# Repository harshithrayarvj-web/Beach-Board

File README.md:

# Beach-Board 
***Journals are separate files in the repo!***

*They contain most of the extra details*

A very dynamic and adaptable keyboard meant to pack as many punches as it can within it's relatively small form factor. Contains a raspberry pi pico, 68 hot-swapable switches, en ec11 rotary encoder, an sd card socket, and a TFT LCD, while being meant to operate on QMK.

# The idea behind it
As much as modern keyboards have numerous shortcuts and even gestures for other inputs, I felt that a centralized unit that could do almost all of those things, and more, could be very useful to quickly do things in a straight forward way, similar to a streamdeck. I plan on leveraging the keyboard layout to make it more moldable and flexible for complex tasks, even if they have many smaller details. Along with this I wanted to expand on how screens could be used on keyboards, instead of basic simple screens that show just one type of data, such as WPM, without much flavor, I wanted to have a screen that could potentially both add to the aesthetics of the keyboard, and provide a functional use depending on the task at hand. The theme of a beach themed "surf board" was because of my first long term profile picture that I drew, it helped me create an identity online, so I wanted to hint at that with my first proper project being a keyboard.

# Characteristics of keyboard
- 68 switches (epomaker creamy jade)
- TFT LCD - animations and information
- 16mb USB C Pi Pico
- Hotswap sockets
- Ortholinear
- Microsd card socket - expanding storage
- ec11 Rotary Encoder
- QMK (keyboard intended to be easily customizable and versatile)

# Schematic

# PCB (silkscreen)

# Firmware (MAINLY WIP)

Need to remake the layout due to losing the tab and being unable to use the other file, or I need to test it on the website again.
Keyboard layout needed to make Firmware development easier with the QMK configurator.

# Notes
The keyboard's case was designed with a good amount of clearance to make up for any tolerance issues, but that might lead to fitment issues, so try to use glue or filler items to help the keyboard come together cleaner. Although the large parts are made with clearance in mind, smaller parts like the screen support might have tight clearances, so don't be afraid to sand it down or cut off some extra bits of plastic if they don't fit.
Pay attention to how and where the small components solder to (resistors, capacitors, or the mcp), and make sure the solder doesn't short.
Try to keep an eye on how high the pico sits on the board to not make it hit the case or put too much stress on the pins if the pins are slightly off from spec, pushing them down too far might put stress on the attachment points for the pins on the pico.

# Reflection
Although the project is overall much simpler than what I aim to do for the future, it definitely helped me kick start PCB designing and showed me how to make a finished product (for the most part). It isn't perfect, and I knew that, especially since how rigid hardware can be could affect it's versatility and how future proof it is, meanwhile software can be improved constantly, and that's why I aimed for a mostly software centric keyboard, and looking back I think my fears are pretty exaggerated and unfounded in some areas, but my general prediction was true, and my lack of skill with designing parts for the case, mounting holes, or clearances showed a lot, however it is something I wish to improve on for future projects, and my keyboard showed me some issues I can look at for now. 

I think the main difficulty with the project that's worse than designing the hardware was rather finding the parts that were cheap but reliable to get, as some parts seemed cheap but did not have a reliable stock, or had enormous shipping fees (though I did have to compromise on a few things for that due to no other alternatives, and a large portion of cost came from shipping itself unfortunately from things like JLPCB and Aliexpress). This project has showed me where to start now with planning for parts and the overall components I could realistically use, something that's harder to be flexible with than even designing parts for a project, like designing the case around a certain screw/hot insert dimension.

There were also easy things that I really enjoyed to do, like placing down the footprints for the pcb, routing, adding silkscreen art, and designing some simple sections of the hardware (especially decoration, like the waves on the screen case), they were mostly enjoyable outside of trying to find settings or tools for a specific action, but I learned to use onshape and kicad decently now. 

Overall, this project really helped me jump into designing something functional and useful, letting me learn to use software like onshape and kicad, and create a BOM and work out issues with how realistic it would be, the experience is really valuable for future projects I plan on doing. The risks I took for this project like using a TFT LCD and a Microsd socket were confusing and scary due to the probability of missing something essential or something that would protect them, but the risk seems worth it as now I know about pull up resistors, decoupling capacitors, ground pour, and how to better go about routing and placing components to make them as clean as possible (but I won't lie, I like how my PCB looks rendered in white with the routes from the MCP, minus the large amount of small route sections visible, but I'm sure cleaner routing is better looking). Using my experience so far, I wish to make more projects and have them come into the real world, hopefully pushing them to be more and more reliable, efficient, and compact.

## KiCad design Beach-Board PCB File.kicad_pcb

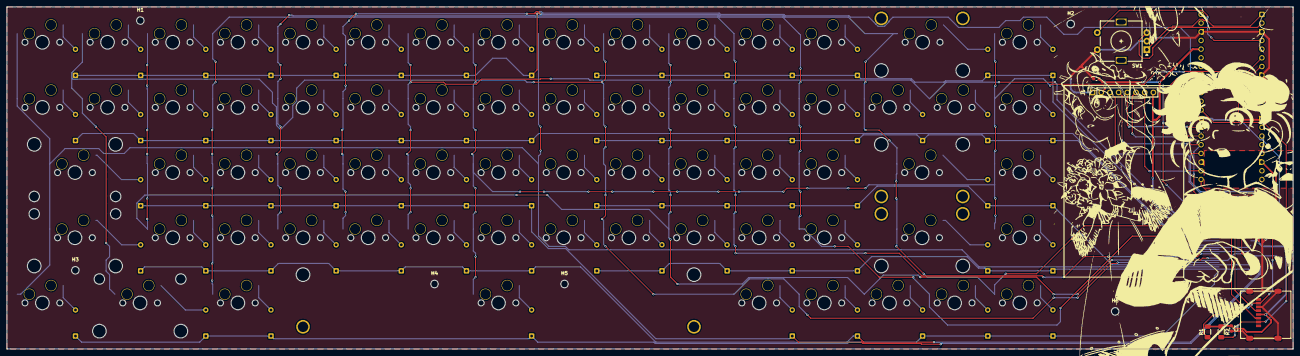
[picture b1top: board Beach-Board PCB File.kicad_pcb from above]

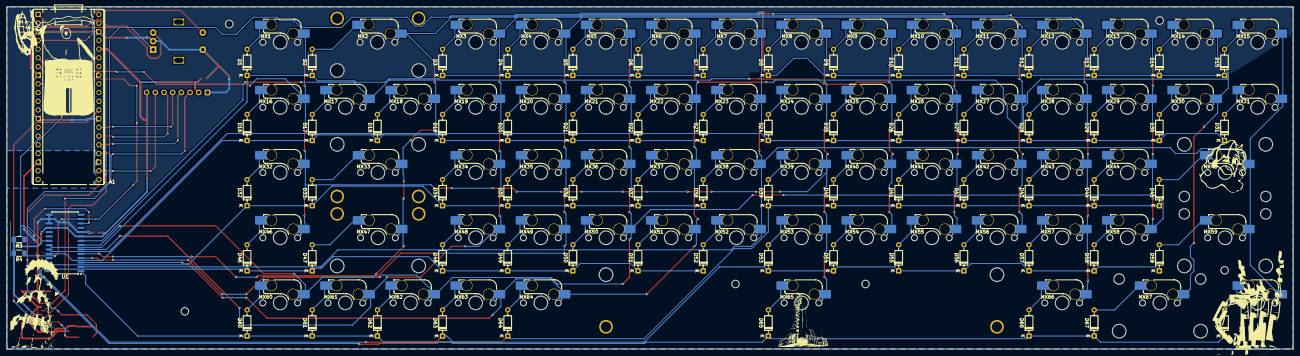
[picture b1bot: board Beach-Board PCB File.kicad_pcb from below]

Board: 2 copper layers, 376.0 x 100.0 mm, 161 parts (147 on the bottom side), 99 nets.

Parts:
A1: RaspberryPi_Pico; RaspberryPi_Pico_Common_THT
C1, C2, C3: 0.1uf; C_0603_1608Metric
D1, D2, D3, D4, D5, D6, D7, D8, D9, D10, D11, D12, D13, D14, D15, D16, D17, D18, D19, D20, D21, D22, D23, D24, D25, D26, D27, D28, D29, D30, D31, D32, D33, D34, D35, D36, D37, D38, D39, D40, D41, D42, D43, D44, D45, D46, D47, D48, D49, D50, D51, D52, D53, D54, D55, D56, D57, D58, D59, D60, D61, D62, D63, D64, D65, D66, D67, D68: 1N4148; D_DO-35_SOD27_P7.62mm_Horizontal
H1, H2, H3, H4, H5, H6: MountingHole; MountingHole_2.2mm_M2
J1: Conn_01x08_Pin; PinSocket_1x08_P2.54mm_Vertical
J2: Micro_SD_Card; microSD_HC_Molex_47219-2001
MX1, MX2, MX3, MX4, MX5, MX6, MX7, MX8, MX9, MX10, MX11, MX12, MX13, MX14, MX15, MX16, MX17, MX18, MX19, MX20, MX21, MX22, MX23, MX24, MX25, MX26, MX27, MX28, MX29, MX30, MX31, MX32, MX33, MX34, MX35, MX36, MX37, MX38, MX39, MX40, MX41, MX42, MX43, MX44, MX45, MX46, MX47, MX48, MX49, MX50, MX51, MX52, MX53, MX54, MX55, MX56, MX57, MX58, MX59, MX60, MX61, MX62, MX63, MX64, MX65, MX66, MX67, MX68: MX_SW_HS; SW_MX_HS_CPG151101S11_1u
R1, R2: 10K; R_1206_3216Metric_Pad1.30x1.75mm_HandSolder
R3, R4: 4.7K; R_1206_3216Metric_Pad1.30x1.75mm_HandSolder
S1, S2, S4: MX_stab; STAB_MX_P_2u
S3, S5, S7: MX_stab; STAB_MX_2u
S6: MX_stab; STAB_MX_P_7u
SW1: RotaryEncoder_Switch; RotaryEncoder_Alps_EC11E-Switch_Vertical_H20mm
U1: MCP23017x-x-SO; SOIC-28W_7.5x17.9mm_P1.27mm

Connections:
/3V3: A1.36 (3V3), C1.1, C2.1, C3.1, J1.2, J1.8, J2.4 (VDD), R1.2, R2.1, R3.2, R4.2, U1.9 (V_{DD}), U1.18 (~RESET)
/CD/DAT3: A1.29 (GPIO22), J2.2 (DAT3/CD), R2.2
/CLK: A1.24 (GPIO18), J1.3, J2.5 (CLK)
/CMD: A1.25 (GPIO19), J1.4, J2.3 (CMD)
/CS: A1.22 (GPIO17), J1.7
/Column_0: MX7.1, MX15.1, MX23.1, MX31.1, MX38.1, MX45.1, MX52.1, MX59.1, MX68.1, U1.2 (GPB1)
/Column_1: MX6.1, MX14.1, MX22.1, MX30.1, MX37.1, MX51.1, MX63.1, MX64.1, MX67.1, U1.3 (GPB2)
/Column_2: MX5.1, MX13.1, MX21.1, MX29.1, MX36.1, MX44.1, MX50.1, MX58.1, MX62.1, U1.4 (GPB3)
/Column_3: MX4.1, MX12.1, MX20.1, MX28.1, MX35.1, MX43.1, MX49.1, MX57.1, MX66.1, U1.5 (GPB4)
/Column_4: MX3.1, MX11.1, MX19.1, MX27.1, MX34.1, MX42.1, MX48.1, MX56.1, MX61.1, U1.6 (GPB5)
/Column_5: MX2.1, MX10.1, MX18.1, MX26.1, MX33.1, MX41.1, MX47.1, MX55.1, MX60.1, U1.7 (GPB6)
/Column_6: MX9.1, MX17.1, MX25.1, MX40.1, MX54.1, U1.8 (GPB7)
/Column_7: A1.9 (GPIO6), MX1.1, MX8.1, MX16.1, MX24.1, MX32.1, MX39.1, MX46.1, MX53.1, MX65.1
/DAT0: A1.21 (GPIO16), J2.7 (DAT0), R1.1
/D/C: A1.26 (GPIO20), J1.6
/RST: A1.27 (GPIO21), J1.5
/Rot-pin_A: A1.1 (GPIO0), SW1.A
/Rot-pin_B: A1.2 (GPIO1), SW1.B
/Rot-pin_S1: A1.4 (GPIO2), SW1.S1
/Row_0: D8.1 (K), D9.1 (K), D10.1 (K), D11.1 (K), D12.1 (K), D13.1 (K), D14.1 (K), D15.1 (K), U1.21 (GPA0)
/Row_1: D1.1 (K), D2.1 (K), D3.1 (K), D4.1 (K), D5.1 (K), D6.1 (K), D7.1 (K), U1.22 (GPA1)
/Row_2: D24.1 (K), D25.1 (K), D26.1 (K), D27.1 (K), D28.1 (K), D29.1 (K), D30.1 (K), D31.1 (K), U1.23 (GPA2)
/Row_3: D16.1 (K), D17.1 (K), D18.1 (K), D19.1 (K), D20.1 (K), D21.1 (K), D22.1 (K), D23.1 (K), U1.24 (GPA3)
/Row_4: D39.1 (K), D40.1 (K), D41.1 (K), D42.1 (K), D43.1 (K), D44.1 (K), D45.1 (K), D64.1 (K), U1.25 (GPA4)
/Row_5: D32.1 (K), D33.1 (K), D34.1 (K), D35.1 (K), D36.1 (K), D37.1 (K), D38.1 (K), U1.26 (GPA5)
/Row_6: D53.1 (K), D54.1 (K), D55.1 (K), D56.1 (K), D57.1 (K), D58.1 (K), D59.1 (K), D63.1 (K), U1.27 (GPA6)
/Row_7: D46.1 (K), D47.1 (K), D48.1 (K), D49.1 (K), D50.1 (K), D51.1 (K), D52.1 (K), U1.28 (GPA7)
/Row_8: D60.1 (K), D61.1 (K), D62.1 (K), D65.1 (K), D66.1 (K), D67.1 (K), D68.1 (K), U1.1 (GPB0)
/SCK: A1.7 (GPIO5), R3.1, U1.12 (SCK)
/SDA: A1.6 (GPIO4), R4.1, U1.13 (SDA)
GND: A1.3 (GND), A1.8 (GND), A1.13 (GND), A1.18 (GND), A1.23 (GND), A1.28 (GND), A1.38 (GND), C1.2, C2.2, C3.2, J1.1, J2.6 (VSS), J2.SH (SHIELD), SW1.C, SW1.S2, U1.10 (V_{SS}), U1.15 (A0), U1.16 (A1), U1.17 (A2)
unnamed: D1.2 (A), MX1.2
unnamed: D2.2 (A), MX2.2
unnamed: D3.2 (A), MX3.2
unnamed: D4.2 (A), MX4.2
unnamed: D5.2 (A), MX5.2
unnamed: D6.2 (A), MX6.2
unnamed: D7.2 (A), MX7.2
unnamed: D8.2 (A), MX8.2
unnamed: D9.2 (A), MX9.2
unnamed: D10.2 (A), MX10.2
unnamed: D11.2 (A), MX11.2
unnamed: D12.2 (A), MX12.2
unnamed: D13.2 (A), MX13.2
unnamed: D14.2 (A), MX14.2
unnamed: D15.2 (A), MX15.2
unnamed: D16.2 (A), MX16.2
unnamed: D17.2 (A), MX17.2
unnamed: D18.2 (A), MX18.2
unnamed: D19.2 (A), MX19.2
unnamed: D20.2 (A), MX20.2
unnamed: D21.2 (A), MX21.2
unnamed: D22.2 (A), MX22.2
unnamed: D23.2 (A), MX23.2
unnamed: D24.2 (A), MX24.2
unnamed: D25.2 (A), MX25.2
unnamed: D26.2 (A), MX26.2
unnamed: D27.2 (A), MX27.2
unnamed: D28.2 (A), MX28.2
unnamed: D29.2 (A), MX29.2
unnamed: D30.2 (A), MX30.2
unnamed: D31.2 (A), MX31.2
unnamed: D32.2 (A), MX32.2
unnamed: D33.2 (A), MX33.2
unnamed: D34.2 (A), MX34.2
unnamed: D35.2 (A), MX35.2
unnamed: D36.2 (A), MX36.2
unnamed: D37.2 (A), MX37.2
unnamed: D38.2 (A), MX38.2
unnamed: D39.2 (A), MX39.2
unnamed: D40.2 (A), MX40.2
unnamed: D41.2 (A), MX41.2
unnamed: D42.2 (A), MX42.2
unnamed: D43.2 (A), MX43.2
unnamed: D44.2 (A), MX44.2
unnamed: D45.2 (A), MX45.2
unnamed: D46.2 (A), MX46.2
unnamed: D47.2 (A), MX47.2
unnamed: D48.2 (A), MX48.2
unnamed: D49.2 (A), MX49.2
unnamed: D50.2 (A), MX50.2
unnamed: D51.2 (A), MX51.2
unnamed: D52.2 (A), MX52.2
unnamed: D53.2 (A), MX53.2
unnamed: D54.2 (A), MX54.2
unnamed: D55.2 (A), MX55.2
unnamed: D56.2 (A), MX56.2
unnamed: D57.2 (A), MX57.2
unnamed: D58.2 (A), MX58.2
unnamed: D59.2 (A), MX59.2
unnamed: D60.2 (A), MX60.2
unnamed: D61.2 (A), MX61.2
unnamed: D62.2 (A), MX62.2
unnamed: D63.2 (A), MX63.2
unnamed: D64.2 (A), MX64.2
unnamed: D65.2 (A), MX65.2
unnamed: D66.2 (A), MX66.2
unnamed: D67.2 (A), MX67.2
unnamed: D68.2 (A), MX68.2
